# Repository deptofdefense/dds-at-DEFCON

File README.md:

# DDS at DEFCON

Welcome, this repo contains the public files for the various DDS defcon workshops amd activities over the years.  Here you can find both gameplay instructions and source code and build guides for if you want to make your own version of something.  

## Quick Links

* DEFCON27 (2019):
    * [Bricks in the Air](https://github.com/deptofdefense/BricksInTheAir)
        * Note the latest version of this workshop is managed by Aerospace Village [here](https://github.com/AerospaceVillage/BricksInTheAir)
* DEFCON28 (2020): 
    * [CPXSimpleSat](https://github.com/deptofdefense/CPXSimpleSat)
    * [DDSat-1](https://github.com/deptofdefense/DDSat)
* DEFCON29 (2021): 
    * [DDRover](https://github.com/deptofdefense/DDRover)
* DEFCON30 (2022): 
    * [Hack the Microgrid](https://github.com/deptofdefense/HackTheMicrogrid)
    * [SpaceJam: Satellite Jamming Simulator](https://github.com/deptofdefense/satellite-jamming-simulator)
* DEFCON31 (2023): 
    * [LLM Rover](https://github.com/zeetwii/llmRover)
* DEFCON32 (2024):
    * [Modal Madness](./modalMadness.md)

## Hacking Libraries

### [Aviation Hacking Library](https://github.com/deptofdefense/hack-aviation-library)
A collection of learning resources for budding aviation security researchers (aka hackers). Learn so we can secure aviation from design to implementation! *Note: This is an evolving resource, so please contribute with a pull request*

### [SAT Hacking library](https://github.com/deptofdefense/hack-a-sat-library)
A collection of Resources for budding SAT hackers (Satellites, not the test ¯\\_(ツ)\_/¯ ). Note: This is an evolving resource, so please contribute with a pull request

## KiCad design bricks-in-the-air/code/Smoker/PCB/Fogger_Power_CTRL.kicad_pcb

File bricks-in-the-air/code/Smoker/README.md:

# Fogger

The fogger is basically a mini improvised fog machine made out of an eSig. It uses fog juice just like a regular fog machine would. The eSig holds the heating coil to vaporize the fog juice. 

This project uses lithium batteries and decently high current (~2-4A) so care should be taken in making this. You are heating a coil up hot enough to boil off fog juice. A controller board has been made to help increase safety but it's up to you to take the necessary precautions and make sure the project is within your skill level to complete safely. You do so entirely at your own risk and no liability his held by any other person or organization. 

Ok, now that that is out of the way let's get to it. 

### Parts
Here are the parts and equipment you need for this project. You can get the parts from anywhere, links to in stock sources at the time of writing have been included for ease. Note, do not substitute the eSIG, or FET without proper analysis to select appropriate replacement components by someone capable of circuit design.  

You will also need several basic tools such as wire strippers, pliers, drill, and a soldering iron with solder. Walk through the instructions below for details of what will have to be done.

| Item | QTY | Example Link to Source |
|----------|----------|-------|
| Kanger Tech T2 Ego eSig |	2 |	[Vaping Zone](https://www.vapingzone.com/kangertech-t2-ego-clearomizer-single-pc.html) |
| Fog juice	| 1	| [Amazon](https://www.amazon.com/FogWorx-Extreme-High-Density-Juice/dp/B0777S56RB/ref=sr_1_5?dchild=1&keywords=fog+juice&qid=1593553743&sr=8-5) |
| Air Pumps W/Tubing | 1 | [Amazon](https://www.amazon.com/gp/product/B06Y2CXZ67/ref=ppx_yo_dt_b_search_asin_title?ie=UTF8&psc=1) |
| 18650 Batteries W/Charger	| 1 |	[Walmart](https://www.walmart.com/ip/EBL-4-Pack-3000mAh-3-7V-Rechargeable-Batteries-Battery-Charger-for-Li-ion-18650-18500-14500-Replacement-Battery/148568497) |
| Wire |	1 |	[Amazon](https://www.amazon.com/Electrical-Flexible-Silicone-different-automotive/dp/B07G744V5Z/ref=sr_1_5?dchild=1&keywords=wire&qid=1593557372&sr=8-5) |
| Shrink Tubing	| 1	| [Amazon](https://www.amazon.com/650pcs-Shrink-Tubing-innhom-Approved/dp/B07WWWPR2X/ref=sr_1_8?dchild=1&keywords=shrink+tubing&qid=1593557287&sr=8-8) |
| FETs (IRLU8743PBF-ND)	| 2	| [Digikey](https://www.digikey.com/product-detail/en/infineon-technologies/IRLU8743PBF/IRLU8743PBF-ND/1894174) |
| Resistors (10K) |	2 |	[Digikey](https://www.digikey.com/product-detail/en/stackpole-electronics-inc/CF14JT10K0/CF14JT10K0CT-ND/1830374) |
| Diodes (P600M-E3-54GICT-ND) |	1 |	[Digikey](https://www.digikey.com/product-detail/en/vishay-semiconductor-diodes-division/P600M-E3-54/P600M-E3-54GICT-ND/3025895) |
| Arduino Mini Pro 5V 16MHz |	1 |	[Sparkfun](https://www.sparkfun.com/products/11113) |
| USB FTDI Breakout |	1 |	[Sparkfun](https://www.sparkfun.com/products/9716) |

### PCB
The PCB is optional and currently in alpha state meaning it has been designed but not yet manufactured and tested. The circuits are simple and can be assembled without a PCB, but it does make things neater and easier. 

The PCB has been designed to be easily made at home either via etching or isolation routing.  

There is also an interactive Bill Of Materials (BOM). Just open the web page and it will highlight the parts selected making it easy to assemble and trace out circuit paths.  

All the PCB files can be found in the PCB folder in this repo. It was designed using KiCAD which is free and open source tool so that everyone has access to the source files for modification.  

**IMPORTANT**  
The only thing that is easy to mess up that could cause damage is inserting the diode incorrectly. Make sure the stripe is facing the correct way as indicated in the photo above. Inserting it backwards will cause a short across the diode when the motor is engaged which can cause components to heat up and potentially cause a fire. Please pay attention to this!

### eSig Modification
This section will walk you through modifying the eSig and connecting the wires needed to drive the coil in it. Originally the T2 is designed to connect to a controller that applies power to it. We are making our own controller in substitution of this. 

**Step 1**
- This is what the eSig looks like fresh out of the package

**Step2**
- There are two breather holes on the side. We will be passing one of the wires through one of the holes.
- You will need to widen the hole slightly. The goal is to make it just big enough for your wire to fit through, without tearing into the insulation.
- If you make the hole too big, don't fret, you can use hot glue, silicone, or other sealant to seal the hole up after. 

**Step 3**
- After passing the wire through the hole, strip off the end and solder it to the middle post
- IMPORTANT:
  - Do not cover the hole with solder or the wire. Air must be able to pass through the hole.
  - Do not let the solder or un-insulated part of the wire touch the outside ring or base, only the middle post. The middle post is one contact of the coil while the outside ring is another. If you do short them, when you turn your smoker on your wires will get very hot and components will be destroyed. 
  - If you are unsure you can use a multimeter to measure the resistance between the wire and the ring. It should be 1.8 ohms or above. If it's lower, you most likely have a short.

**Step 4**
- Here you will cover the second hole to prevent air leaks and use that cover to connect the second wire
- Use something sharp to scrape off the chrome plating so that solder will stick to it.

**Step 5**
- Solder the second wire to the plug
- You can now take the mouthpiece off the second eSig and place it on the back of your smoker. 

Congratulations, your modified eSig is now ready for the electrical assembly. 

### Electrical Assembly (No PCB)
While a PCB design is underway to make assembly easier, the control circuit has also been designed so that you don't need to make a PCB to create the Smoker.

**Step 1**
- Attach the Resistor to a FET as shown
- This is a pulldown resistor that keeps the FET off while the trigger line is floating

**Step 2**
- Remember when connecting things to put the heat-shrink on the wire before soldering so you can slide it down and heat it up to secure it. If you forget, you will have to pull the wire off and re-solder it all over again.

**Step 3**
- Solder one of the blue wires (preferably the one connected to the outside of the unit plunging the hole) to the middle terminal on the FET.

**Step 4**
- Move the heat shrink up making sure that there is no exposed wire or solder that could touch the other two contacts. 
- Use a heatgun to shrink the tubing.

**Step 5**
- Solder a green and black wire to the other two connectors
- The FET is still face up in this image, the green wire is connected to the left pin while the blue to the right.
- Cover the whole assembly with shrink tubing to protect it.

**Step 6**
- The pump has a red dot next to it's positive terminal
- Wrap the diode around the two terminals as shown
- IMPORTANT
  - The diode MUST be put on in the right direction. The silver line must be pointing to the positive side.
  - Make sure the metal terminals do not contact the metal casing.
  - If this is put on backwards you will get a nice pop out of the diode as it heats up to red hot conditions. 
- Connect a red and black wire to the the positive and negative terminals as shown. 
- Shrink tube to cover and protect the contacts.

**Step 7**
- Assemble the second FET just like you did the first FET with the pulldown resistor.
- Connect the negative (Black) wire to the center post of the FET.
- Connect a green wire to the left and a black wire to the right pins as shown
- When done, place a piece of shrink tubing over the FET to protect it.

**Step 8**
- Connect the two negative (Black) wires together as shown
- Connect the two positive (Red and Blue) wires together as shown

**Step 9**
- Solder the negative and positive wires to the negative and positive terminals of the battery (Do this with NO battery installed)
- IMPORTANT
  - Be sure to get the polarity correct and don't mix up positive and negative. There are markings on the inside of the battery holder but they are small.
  - If you need to add labels to the battery holder to make sure your battery gets inserted correctly.
  - If you put the battery in backwards the smoker and motor will automatically turn on, the motor will run in reverse, and the FETS will likely be damaged if left on for too long.

**Step 10**
- Time to test the smoker before connecting to the controller!
- Add some fog juice to the smoker by removing the top mouthpiece.
- Add a section of tubing from the pump kit to connect the pump to the eSig.
- Allow time for the wick to soak up the juice, you can shake it up a bit to help it but not too much.
- Make sure the smoker is pointing upward. Ideally even more upright than in this image.
- The two green wires are trigger wires. You can connect them to the positive side of the battery to turn the circuit on to test it. 
- If you hear crackling from the smoker but it's not putting much out, the wick got too wet. (You did keep it upright, right?) If that happens you can blow into the mouthpiece (with it off!) and a few drops of fluid will be pushed away from the coil. Try it again, it should now smoke

### Connecting the Controller
This section is in progress and needs some photos but luckily the steps are not too hard and I have faith you can figure these out in the mean time. 

- Be sure you removed the battery before continuing
- Solder on a black wire to the negative side of the battery
- Connect the other side of that wire to the GND pin of the Arduino Pro Mini (Either one of the two listed above will work)
- Solder on a red wire to the positive side of the battery
- Connect the other side of that wire to the VCC pin of the Arduino Pro Mini
  - Note: Make sure you did buy the 5V version of the Arduino Pro Mini. If not, powering from the battery on VCC will cause damage!
  - Note, the Arduino Pro Mini is rated to be run at 5V. However, a fully charged LI-ION battery like the 18650 we have has a max voltage of about 4.2V. The battery can drain as low as 3.5V on average. In testing, the Arduino Pro Mini operates stability as far down as 2.2V. So powering VCC directly from the battery should be sufficient.
  - If you are wondering why not pick the 3.3V version of the Arduino Pro Mini and power through the RAW pin which has a regulator to run everything at 3.3V, then you are clever but there is one gotcha. The FET resistance at a gate voltage of 3.3V is much higher than that of the 4.2V. In order to simplify the circuitry and reduce FET heat output, we are maximizing the gate drive voltage. As the Arduino was stable at much lower voltages, this we the simplest compromise. 
- Connect the green wire that controls the Pump to Pin 10 of the Arduino
- Connect the green wire that controls the eSig to Pin 11 of the Arduino
- Connect a black wire to the other GND pin of the Arduino
- Connect a wire of your choosing to pin 9 of the Arduino.
  - This is your trigger pin
  - When this pin goes high, the smoker will run for the specified amount of time
  - IMPORTANT
    - This pin has no pulldown resistor on it, so if it's not connected to a signal source, it will repeatedly trigger the fogger. 
    - You can either add a 10K resistor between the GND wire and the trigger line, or make sure the line is connected to the source signal that will drive it high and low as needed.
    - It's up to you to design what this is connecting to and how you trigger it. A simple way would be connect a button to the trigger line that connects it to VCC when the button is pressed (remember to add that resistor to pull it back down when the button is not being pressed).
    
Wiring is now done! Congratulations!

### Programming and Configuring the fog controller
The Arduino Pro Mini must now be uploaded with the firmware. 
There are lots of good tutorials for hooking up the Aruino Pro Mini and configuring the Arduino IDE.   [Here is one](https://www.arduino.cc/en/Guide/ArduinoProMini)  

The Basic FTDI board in the parts list was used to program and configure the board.

The code is located in this folder inside of the Code directory.

The controller has configurable parameters that can be adjusted. The parameters will be remembered even if the battery is disconnected and the board is restarted. To configure the board, use the serial terminal in the Arduino IDE. When opened, you should see the following instructions printed out in the terminal. 

Good luck and have fun!

```
Saved State Found, populating settings
 
Instructions:
The first letter is the command
The numbers following the letter (if applicable) is the setting
For example p50 will set the pump to 50% duty
Warning, it's up to you to make sure you supply adiquate air
for the fog level. You also need to make sure you don't run 
the fogger too long or you can cause a hazardus condition. 
Make sure you allow enough cooldown time also.
Fogger control pin is : 11
Pump control pin is : 10
Trigger pin is : 9
 
Default Settings:
Pump % = 255
Fog % = 255
Run time [s] = 20
Cooldown time [s] = 5
 
Current Settings:
Pump % = 255
Fog % = 255
Run time [s] = 5
Cooldown time [s] = 1
---------------------------------------------------------------
P### - Set pump speed %     (range 0-255)
F### - Set fog level %      (range 0-255)
R### - Max Run Time Seconds (range 0-255)
C### - Set Cooldown time    (range 0-255)
D    - Reset all to default
T    - Manually Trigger Fogger

```

# Future Improvements
- 3D print a tube adapter for the back so that you don't need two eSig's to make one smoker
- Add images of the controller wiring
- Improve the programming and settings walkthrough
- Add schematic and PCB for the smoker circuit

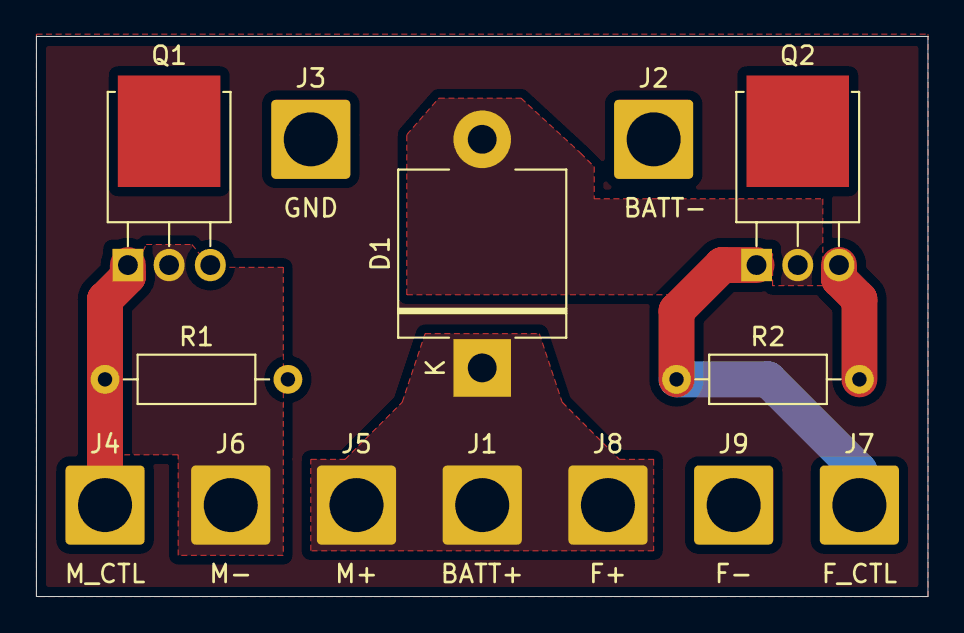
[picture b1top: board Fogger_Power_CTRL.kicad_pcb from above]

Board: 2 copper layers, 49.5 x 31.1 mm, 14 parts (0 on the bottom side), 6 nets.

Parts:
D1: NA; D_P600_R-6_P12.70mm_Horizontal
J1: Batt +; SolderWire-2.5sqmm_1x01_D2.4mm_OD4.4mm
J2: Batt -; SolderWire-2.5sqmm_1x01_D2.4mm_OD4.4mm
J3: Control_GND; SolderWire-2.5sqmm_1x01_D2.4mm_OD4.4mm
J4: Control_Smoke; SolderWire-2.5sqmm_1x01_D2.4mm_OD4.4mm
J5: Smoke +; SolderWire-2.5sqmm_1x01_D2.4mm_OD4.4mm
J6: Smoke -; SolderWire-2.5sqmm_1x01_D2.4mm_OD4.4mm
J7: Control_Motor; SolderWire-2.5sqmm_1x01_D2.4mm_OD4.4mm
J8: Motor +; SolderWire-2.5sqmm_1x01_D2.4mm_OD4.4mm
J9: Motor -; SolderWire-2.5sqmm_1x01_D2.4mm_OD4.4mm
Q1, Q2: IRLU8743PBF-ND; TO-251-3-1EP_Horizontal_TabDown
R1, R2: 10K; R_Axial_DIN0207_L6.3mm_D2.5mm_P10.16mm_Horizontal

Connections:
+BATT: D1.1, J1.1, J5.1, J8.1
GNDREF: J2.1, J3.1, Q1.3, Q2.3, R1.2, R2.2
unnamed: D1.2, J9.1, Q2.2
unnamed: J4.1, Q1.1, R1.1
unnamed: J6.1, Q1.2
unnamed: J7.1, Q2.1, R2.1

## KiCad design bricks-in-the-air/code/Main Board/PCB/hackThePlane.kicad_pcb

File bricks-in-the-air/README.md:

# Bricks In The Air Workshop Files

In order to encourage more people to become interested in investigating aircraft vulnerabilities as well as understand the problems aircraft face, Bricks in the Air attempts to represent this problem in a simple and jargon free manner.  By replacing the complex and unfamiliar 1553/429 buses with the more well known I2C data bus, we remove a lot of the jargon and confusion of the problem while allowing attendees to understand the core problem: Aircraft data buses are old and unsecure, and someone should fix that.  

As a part of the modifications for Safe Mode a twitch chat will act as a replacement for the I2C link to the kit.  As such the user will enter I2C commands via the IRC chat of the hosting Twitch channel instead of their serial terminal.  
© 2020 GitHub, Inc.

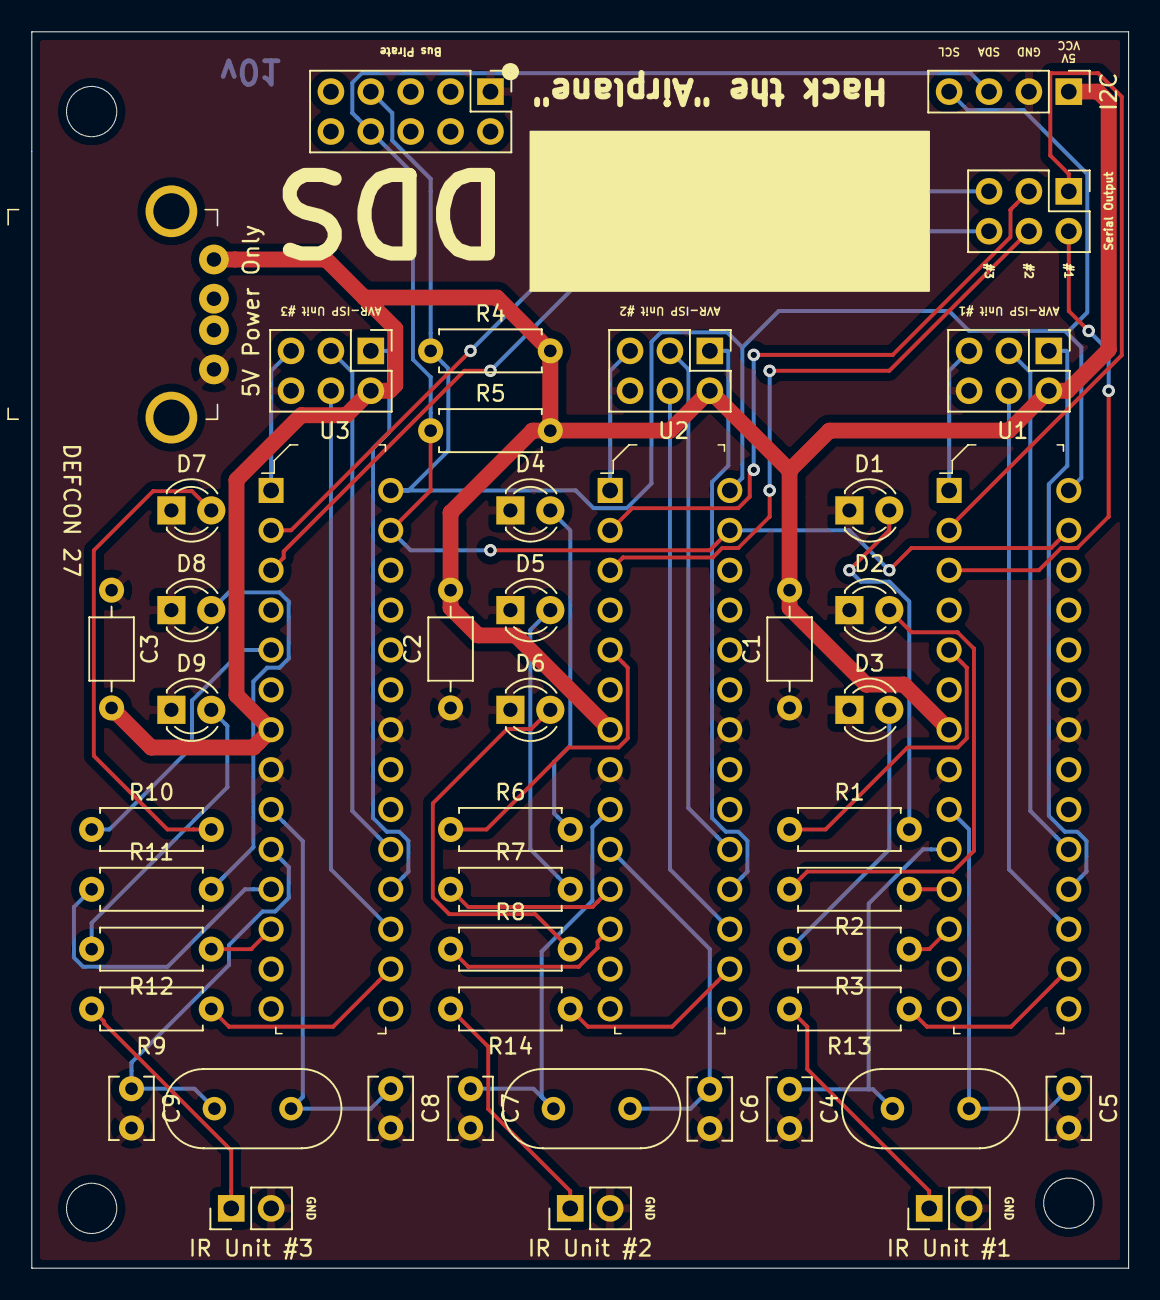
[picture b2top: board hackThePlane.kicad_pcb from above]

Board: 2 copper layers, 69.8 x 78.7 mm, 48 parts (0 on the bottom side), 52 nets.

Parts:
C1, C2, C3: .1uF; C_Axial_L3.8mm_D2.6mm_P7.50mm_Horizontal
C4, C5, C6, C7, C8, C9: 22pf; C_Disc_D3.8mm_W2.6mm_P2.50mm
D1, D2, D3, D4, D5, D6, D7, D8, D9: LED; LED_D3.0mm
J1, J4, J6: AVR-ISP-6; PinHeader_2x03_P2.54mm_Vertical
J2: Conn_02x05_Counter_Clockwise; PinHeader_2x05_P2.54mm_Vertical
J3: Conn_01x04; PinHeader_1x04_P2.54mm_Vertical
J5, J7, J8: Conn_01x02; PinHeader_1x02_P2.54mm_Vertical
J9: USB_A; USB_A_Female_UE27AC54100
J10: Conn_02x03_Counter_Clockwise; PinHeader_2x03_P2.54mm_Vertical
R1, R2, R3, R6, R7, R8, R10, R11, R12: 330; R_Axial_DIN0207_L6.3mm_D2.5mm_P7.62mm_Horizontal
R4, R5: 4.7k; R_Axial_DIN0207_L6.3mm_D2.5mm_P7.62mm_Horizontal
R9, R13, R14: 100; R_Axial_DIN0207_L6.3mm_D2.5mm_P7.62mm_Horizontal
U1, U2, U3: ATmega328P-PU; DIP-28_W7.62mm
Y1, Y2, Y3: Crystal; Crystal_HC49-U_Vertical

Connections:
GND: C1.1, C2.1, C3.1, C4.2, C5.2, C6.2, C7.2, C8.2, C9.2, D1.1, D2.1, D3.1, D4.1, D5.1, D6.1, D7.1, D8.1, D9.1, J1.6, J2.1, J3.2, J4.6, J5.2, J6.6, J7.2, J8.2, J9.4, U1.8, U1.22, U2.8, U2.22, U3.8, U3.22
unnamed: C4.1, U1.10, Y1.2
unnamed: C5.1, U1.9, Y1.1
unnamed: C6.1, U2.10, Y2.2
unnamed: C7.1, U2.9, Y2.1
unnamed: C8.1, U3.9, Y3.1
unnamed: C9.1, U3.10, Y3.2
unnamed: D1.2, R1.2
unnamed: D2.2, R2.2
unnamed: D3.2, R3.2
unnamed: D4.2, R6.2
unnamed: D5.2, R7.2
unnamed: D6.2, R8.2
unnamed: D7.2, R10.2
unnamed: D8.2, R11.2
unnamed: D9.2, R12.2
unnamed: J1.1, U1.18
unnamed: J1.3, U1.19
unnamed: J1.4, U1.17
unnamed: J1.5, U1.1
unnamed: J2.7, J3.4, R4.1, U1.28, U2.28, U3.28
unnamed: J2.8, J3.3, R5.1, U1.27, U2.27, U3.27
unnamed: J4.1, U2.18
unnamed: J4.3, U2.19
unnamed: J4.4, U2.17
unnamed: J4.5, U2.1
unnamed: J5.1, R9.2
unnamed: J6.1, U3.18
unnamed: J6.3, U3.19
unnamed: J6.4, U3.17
unnamed: J6.5, U3.1
unnamed: J7.1, R13.2
unnamed: J8.1, R14.2
unnamed: J10.1, U1.2
unnamed: J10.2, U1.3
unnamed: J10.3, U2.2
unnamed: J10.4, U2.3
unnamed: J10.5, U3.2
unnamed: J10.6, U3.3
unnamed: R1.1, U1.5
unnamed: R2.1, U1.11
unnamed: R3.1, U1.12
unnamed: R6.1, U2.5
unnamed: R7.1, U2.11
unnamed: R8.1, U2.12
unnamed: R9.1, U3.16
unnamed: R10.1, U3.5
unnamed: R11.1, U3.11
unnamed: R12.1, U3.12
unnamed: R13.1, U1.16
unnamed: R14.1, U2.16
VCC: C1.2, C2.2, C3.2, J1.2, J3.1, J4.2, J6.2, J9.1, R4.2, R5.2, U1.7, U2.7, U3.7

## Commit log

2020-07-07 Create bricks-in-the-air
2020-07-07 Delete bricks-in-the-air
    need a folder
2020-07-09 Adding libraries
2020-07-29 cpx update
2020-07-30 added photos and started build guide
2020-07-31 added build guide
2020-07-31 fuxed typos
2020-08-03 Add files via upload
    Added initial BIA ICD
2020-08-03 Update README.md
    Added link to simple SAT
2020-08-03 Update README.md
    Updated description with bricks in the air
2020-08-03 Updated ReadMe with links to DDSAT and NyanSat
2020-08-04 Banner and footer images
2020-08-04 Added Banner logo
2020-08-04 Added footer image in ReadMe
2020-08-04 Updating content and formatting
    -reorged headers
    - edited information to focus on the ICDS
2020-08-04 Simplified gameplay header
2020-08-04 Adding cpx sat notes
2020-08-04 Adding bonus notes
    - [Bonus Notes](./BONUS-cpx-sat-notes.pdf)
2020-08-04 adding Nyansat link to external window
2020-08-04 working on target window
    (https://nyan-sat.com/){:target="_blank"}
2020-08-04 still playing with target
2020-08-04 adding bold to workshop names
2020-08-04 adding link to nyansat site
2020-08-04 Adding Aviation Hacking Library
2020-08-04 updated file
    dan's fixes + live links
2020-08-05 Update README.md
    fixed the markdown shoulder... extra escape character
2020-08-07 Fixed typo "manor" to "manner"
2020-08-11 added code
2020-08-12 added info
2020-08-12 added link
2020-08-12 test
2020-08-13 added encoding description
2020-08-28 cut over from working repo.
2021-07-26 quick reorg
2021-07-27 edits
2021-08-02 quick edit
2021-08-02 added photos
2021-08-08 added source code
2021-08-12 added 3d files and instructions
2022-07-26 Added DC30 Space Jam resources
2022-07-26 Make submodule track main
2022-07-26 Added Aerospace Village Eavesdropping Workshop Contents
2022-07-28 placeholder
2022-07-29 added stl files
2022-08-08 writing
2022-08-09 code dump
2022-08-12 code update
2022-08-16 Update README.md
    Broken Space Jam link. Converted from TODO ADD LINK to the correct content location.
2022-08-18 updated stls
2022-08-22 pics
2022-08-30 game explination
2022-08-30 houses
2022-09-02 added solar and turbine info
2022-09-13 quick change
2022-09-13 cleanup
2022-09-19 photos
2023-05-22 Create CNAME
2023-05-22 quick edit
    updated index redirect text
2023-08-02 temp
2023-08-07 edit
2023-09-11 breaking out each project into their own repo
2023-09-12 Update README.md
    fixed emoji
2024-08-08 updated for DC32
